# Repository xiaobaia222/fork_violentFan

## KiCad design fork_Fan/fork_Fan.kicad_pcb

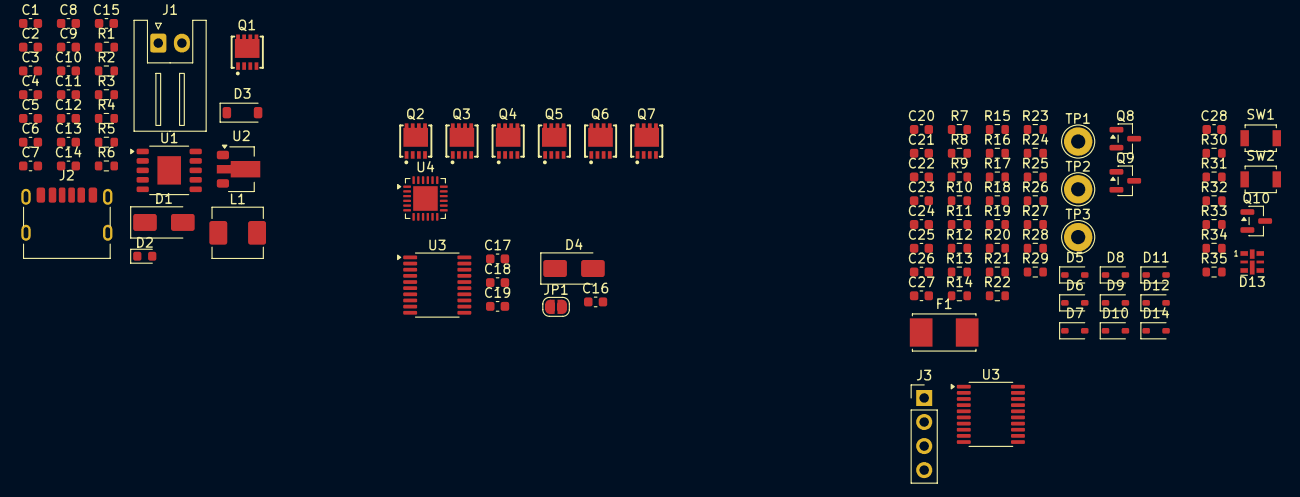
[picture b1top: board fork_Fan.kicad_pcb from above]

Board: 2 copper layers, 103 parts (0 on the bottom side), 48 nets, no tracks yet.

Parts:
C1, C3, C5, C6, C7, C8, C10, C11, C12, C14, C26, C27: 10uF; C_0603_1608Metric
C2, C4, C9, C13, C15, C16, C19, C28: 100nF; C_0603_1608Metric
C17, C18: 22uF; C_0603_1608Metric
C20, C21, C22: 10nF; C_0603_1608Metric
C23, C24, C25: 1uF; C_0603_1608Metric
D1, D4: SS54; D_SMA
D2: LED; LED_0603_1608Metric
D3: BZT52B5V6; D_SOD-123
D5, D6, D7, D8, D9, D10, D11, D12, D14: 1N5819WS; D_SOD-323
D13: APA102-2020; LED-APA102-2020
F1: Fuse; Fuseholder_Littelfuse_Nano2_157x
J1: Conn_01x02; JST_XH_S2B-XH-A_1x02_P2.50mm_Horizontal
J2: USB_C_Receptacle_PowerOnly_6P; USB_C_Receptacle_HRO_TYPE-C-31-M-17
J3: Conn_01x04; PinHeader_1x04_P2.54mm_Vertical
JP1: SolderJumper_2_Open; SolderJumper-2_P1.3mm_Open_RoundedPad1.0x1.5mm
L1: 2.2uH; L_APV_APH0530
Q1, Q2, Q3, Q4, Q5, Q6, Q7: Q_NMOS; PDFN-8_L3.3-W3.3-P0.65-BL-DSG
Q8: AO3401A; SOT-23
Q9, Q10: SS8050; SOT-23
R1, R2, R4, R5: 5.1K; R_0603_1608Metric
R3: 7.5K; R_0603_1608Metric
R6, R33: 100K; R_0603_1608Metric
R7, R8, R9, R10, R11, R12: 5.1R; R_0603_1608Metric
R13, R14, R15, R16, R17, R18, R19, R20, R21, R22, R23, R24, R28, R31: 10K; R_0603_1608Metric
R25, R26, R27, R29, R30, R34, R35: 2K; R_0603_1608Metric
R32: 200K; R_0603_1608Metric
SW1, SW2: SW_Push; SW_SPST_B3U-1000P
TP1, TP2, TP3: TestPoint; TestPoint_THTPad_D3.0mm_Drill1.5mm
U1: CS5086E; SSOP-10-1EP_3.9x4.9mm_P1mm_EP2.5x3.0mm
U2: HT7150-1; SOT-89-3
U3: STC8G1K08-38I-TSSOP20; TSSOP-20_4.4x6.5mm_P0.65mm
U3#2: STC8H1K08-38I-TSSOP20; TSSOP-20_4.4x6.5mm_P0.65mm
U4: FD6288Q; QFN-24-1EP_4x4mm_P0.5mm_EP2.6x2.6mm

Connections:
+5V: C14.1, C15.1, C17.1, C18.1, C19.1, D13.1 (VDD), J3.1, U2.3 (VOUT), U3.8 (VCC), U3#2.8 (VCC), U3#2.9 (ADC_VRef+)
/IO_opera/bat_sample: C28.1, R34.1
/motor_driver/A: C23.2, Q2.D, Q3.S, R13.2, R19.1, TP1.1, U4.18 (VS1)
/motor_driver/ADC11: C20.2, R19.2, R22.1, R25.1
/motor_driver/ADC12: C21.2, R20.2, R23.1, R26.1
/motor_driver/ADC13: C22.2, R21.2, R24.1, R27.1
/motor_driver/B: C24.2, Q4.D, Q5.S, R14.2, R20.1, TP2.1, U4.15 (VS2)
/motor_driver/C: C25.2, Q6.D, Q7.S, R18.2, R21.1, TP3.1, U4.12 (VS3)
/motor_driver/COMP-: R22.2, R23.2, R24.2
/motor_driver/M_A_H1: D5.1 (K), R7.1, U4.19 (HO1)
/motor_driver/M_A_L1: D6.1 (K), R8.1, U4.11 (LO1)
/motor_driver/M_B_H2: D7.1 (K), R9.1, U4.16 (HO2)
/motor_driver/M_B_L2: D8.1 (K), R10.1, U4.10 (LO2)
/motor_driver/M_C_H3: D9.1 (K), R11.1, U4.13 (HO3)
/motor_driver/M_C_L3: D10.1 (K), R12.1, U4.9 (LO3)
/motor_driver/VB_A: C23.1, D14.1 (K), U4.20 (VB1)
/motor_driver/VB_B: C24.1, D11.1 (K), U4.17 (VB2)
/motor_driver/VB_C: C25.1, D12.1 (K), U4.14 (VB3)
/stc_mcu/RX: J3.4, U3#2.12 (TxD/ADC9/P3.1)
/stc_mcu/TX: J3.3, U3#2.11 (INT4/RxD/ADC8/P3.0)
GND: C1.2, C2.2, C3.2, C4.2, C5.2, C6.2, C7.2, C8.2, C9.2, C10.2, C11.2, C12.2, C13.2, C14.2, C15.2, C16.2, C17.2, C18.2, C19.2, C20.1, C21.1, C22.1, C26.2, C27.2, C28.2, D3.2 (A), D13.6 (GND), J2.A12 (GND), J2.B12 (GND), J2.S1 (SHIELD), J3.2, Q1.S, Q3.D, Q5.D, Q7.D, Q9.2 (E), Q10.2 (E), R1.2, R2.2, R3.2, R15.2, R16.2, R17.2, R25.2, R26.2, R27.2, R33.2, SW1.2, SW2.2, U1.4 (AGND), U1.11 (EP), U2.1 (GND), U3.10 (GND), U3#2.10 (GND), U4.6 (COM)
unnamed: D1.2 (A), L1.2, U1.5 (LX)
unnamed: C3.1, C4.1, C5.1, C6.1, D1.1 (K), U1.6 (VBS)
unnamed: D2.2 (A), R4.2
unnamed: D2.1 (K), R5.2, U1.2 (STAT)
unnamed: C16.1, D3.1 (K), JP1.2 (B)
unnamed: C12.1, C13.1, D4.1 (K), U2.2 (VIN)
unnamed: D5.2 (A), Q2.G, R7.2, R13.1
unnamed: D6.2 (A), Q3.G, R8.2, R15.1
unnamed: D7.2 (A), Q4.G, R9.2, R14.1
unnamed: D8.2 (A), Q5.G, R10.2, R16.1
unnamed: D9.2 (A), Q6.G, R11.2, R18.1
unnamed: D10.2 (A), Q7.G, R12.2, R17.1
unnamed: F1.2, Q2.S, Q4.S, Q6.S
unnamed: J2.A5 (CC1), R1.1
unnamed: J2.B5 (CC2), R2.1
unnamed: JP1.1 (A), Q1.G, R6.2
unnamed: Q8.1 (G), Q9.3 (C), R28.2
unnamed: Q9.1 (B), R29.1
unnamed: Q10.1 (B), R31.2
unnamed: R30.2, SW1.1
unnamed: R32.2, R33.1, R34.2
unnamed: R35.2, SW2.1
unnamed: R3.1, U1.10 (ICHG)
P_GND: J1.2, Q1.D
VBUS: C1.1, C2.1, C7.1, J2.A9 (VBUS), J2.B9 (VBUS), L1.1, R4.1, R31.1, U1.3 (VIN)
VDRV: C26.1, C27.1, D11.2 (A), D12.2 (A), D14.2 (A), Q8.3 (D), U4.4 (VCC)
Vbat: C8.1, C9.1, C10.1, C11.1, D4.2 (A), F1.1, J1.1, Q8.2 (S), R6.1, R28.1, R32.1, U1.7 (BAT)

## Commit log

2026-01-29 init fork file
2026-01-29 power and chrg complete
2026-01-29 add mcu and some motor driver need bat sample, key, programing pad, fuse, fd6288 power.
2026-01-31 完善原理图，还未完成
2026-01-31 fix gitignore
2026-02-11 fix code
2026-03-04 使用cursor完成按键的功能
2026-03-04 电机可以启动，但是第一档有点不顺滑，会突变一下
2026-03-04 AI学习am32代码改进原来的代码
2026-04-04 暂时提交
2026-04-04 重构主循环状态机，修复开机无反应问题
    - 将 STA_* 位标志替换为互斥枚举 state_t（SLEEP/CHARGING/RUNNING），
    消除非法状态组合，状态转移逻辑更清晰
    - 消除 STA_WAKING 中间状态，key_handle() 直接判断 VBUS_SENSE 完成转移，
    修复原设计 key_handle 与 tick 时序不同步的竞态问题
    - 修复 POWER_SWITCH 在 init() 中提前置 0 导致上电 LED 双闪不可见
    - 修复 P3.0 (VBUS_SENSE) 悬空误判充电线接入，导致长按后立即返回休眠
2026-04-04 低功耗优化：掉电模式 + WKTR 喂狗
    休眠/充电时进入 PDN 掉电模式（PCON|=0x02）而非空闲模式：
    - sleep_enter()：关闭 Timer2/Timer0/Timer1、ADC、比较器，
    启动掉电唤醒定时器（WKTCL/WKTCH，约 100ms/次，32KHz）
    - sleep_exit() ：关闭 WKTR，重启 Timer2，恢复 ADC 和比较器
    - 掉电期间 WDT 暂停；WKTR 每 100ms 唤醒后立即喂狗（WDT_PS=7）
    - 睡眠中按键通过 100ms 轮询检测（10 次 = 1s 长按），
2026-04-04 修复开机后立即关机：长按松手后再切换到运行模式
2026-04-12 修改掉电唤醒定时器，恢复中断，计时器等，还没好
2026-04-12 问题在按键要先于motor初始化，估计是两个没有完全解耦
2026-06-02 struct 3d and change speed
